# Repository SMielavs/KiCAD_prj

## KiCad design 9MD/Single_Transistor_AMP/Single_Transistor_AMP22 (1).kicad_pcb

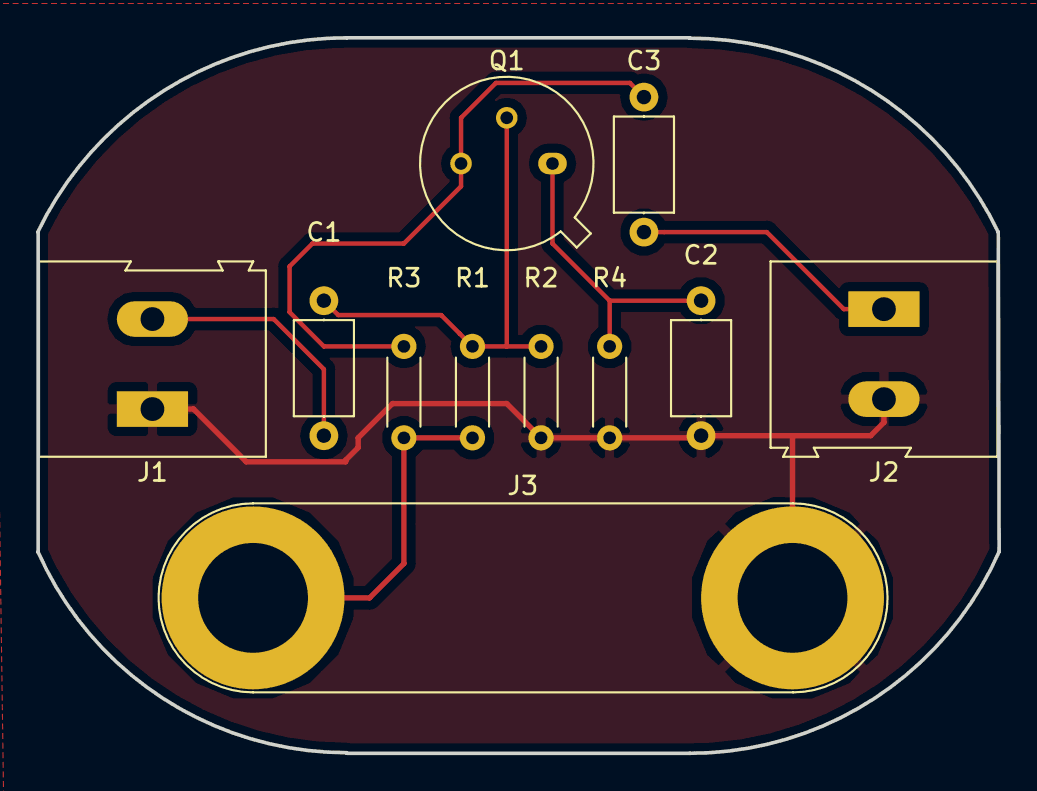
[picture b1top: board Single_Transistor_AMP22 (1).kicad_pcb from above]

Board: 2 copper layers, 53.4 x 39.8 mm, 11 parts (0 on the bottom side), 7 nets.

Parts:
C1, C3: 20uF; C_Axial_L5.1mm_D3.1mm_P7.50mm_Horizontal
C2: 50uF; C_Axial_L5.1mm_D3.1mm_P7.50mm_Horizontal
J1: Signal_In; TerminalBlock_Altech_AK300-2_P5.00mm
J2: Signal_Out; TerminalBlock_Altech_AK300-2_P5.00mm
J3: Screw_Terminal_01x02; Banana_Jack_2Pin
Q1: 2N2219; TO-39-3
R1: 22k; R_Axial_DIN0204_L3.6mm_D1.6mm_P5.08mm_Horizontal
R2: 6.8k; R_Axial_DIN0204_L3.6mm_D1.6mm_P5.08mm_Horizontal
R3: 4.7k; R_Axial_DIN0204_L3.6mm_D1.6mm_P5.08mm_Horizontal
R4: 1.8k; R_Axial_DIN0204_L3.6mm_D1.6mm_P5.08mm_Horizontal

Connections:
+12V: J3.1, R1.1, R3.1
GND: C2.2, J1.1, J2.2, J3.2, R2.2, R4.2
unnamed: C1.1, Q1.2, R1.2, R2.1
unnamed: C1.2, J1.2
unnamed: C2.1, Q1.1, R4.1
unnamed: C3.1, J2.1
unnamed: C3.2, Q1.3, R3.2

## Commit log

2019-03-13 Pieveinots 3. majasdarbs
2019-05-01 Add files via upload
    Pievienots 4. majasdarbs
2019-05-08 Add files via upload
    Pievienots 5. mājasdarbs
2019-05-08 Pievienots 6. mājasdarbs (7. lekcija)
2019-06-12 Izlabots 3MD
2019-06-12 Izlabots 4MD
2019-06-12 Izlabots 5MD
2019-06-12 Izlabots 6MD
2019-06-12 Pievienots 7MD
2019-06-12 Pievienots 8MD
2019-06-12 Pievienots 9MD
2019-06-12 Pievienots 10MD
2019-06-13 Pievienots kursa darbs
